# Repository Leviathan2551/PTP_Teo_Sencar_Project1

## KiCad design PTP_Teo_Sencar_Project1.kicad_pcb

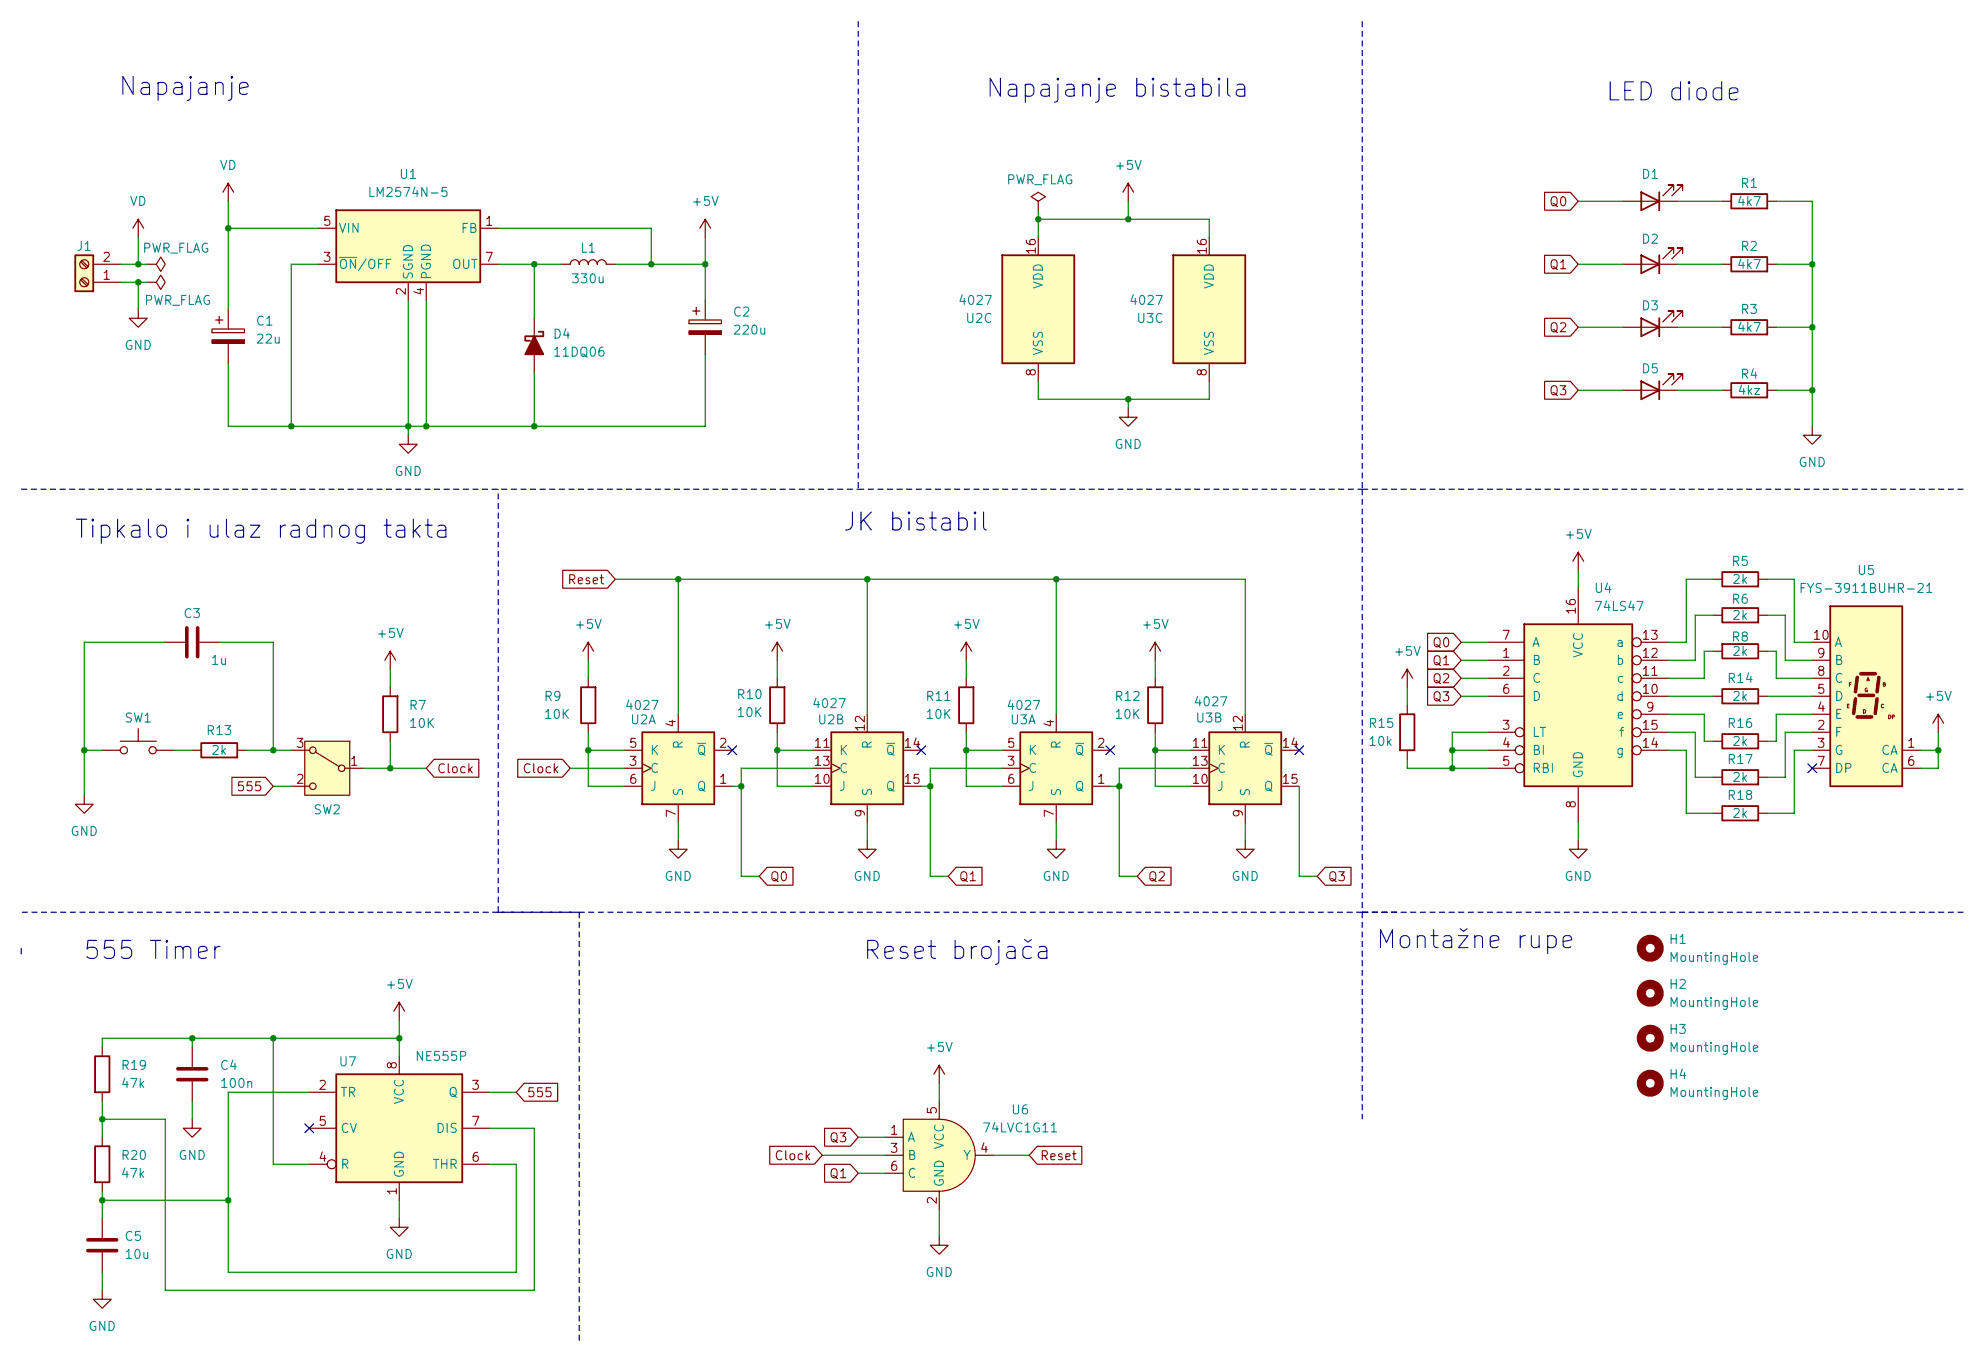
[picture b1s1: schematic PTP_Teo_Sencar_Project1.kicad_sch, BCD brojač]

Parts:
C1: 22u; CP_Radial_D5.0mm_P2.00mm; Manufacturer Part Number EWH1EM220D11OT
C2: 220u; CP_Radial_D5.0mm_P2.00mm; Manufacturer Part Number RD1A227M05011BB
C3: 1u; C_1206_3216Metric_Pad1.33x1.80mm_HandSolder; Manufacturer Part Number CL31B105KBHNNNE
C4: 100n; C_1206_3216Metric_Pad1.33x1.80mm_HandSolder; Manufacturer Part Number CL31B104KBCNNNC
C5: 10u; C_1206_3216Metric_Pad1.33x1.80mm_HandSolder; Manufacturer Part Number CL31A106KBHNNNE
D1, D2, D3, D5: LED; LED_D5.0mm
D4: 11DQ06; D_DO-41_SOD81_P12.70mm_Horizontal; Manufacturer Part Number 11DQ06TA
H1, H2, H3, H4: MountingHole; MountingHole_5.5mm
J1: Screw_Terminal_01x02; TerminalBlock_MetzConnect_Type011_RT05502HBLC_1x02_P5.00mm_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; Manufacturer Part Number DG301-5.0-02P-12-00A(H)
L1: 330u; L_Radial_D7.2mm_P3.00mm_Murata_1700; Manufacturer Part Number COIL0608-0.33
R1, R2, R3: 4k7; R_Axial_DIN0207_L6.3mm_D2.5mm_P10.16mm_Horizontal
R4: 4kz; R_Axial_DIN0207_L6.3mm_D2.5mm_P10.16mm_Horizontal
R5, R6, R8, R13, R14, R16, R17: 2k; R_1206_3216Metric_Pad1.30x1.75mm_HandSolder; Manufacturer Part Number 1206S4F2001T5E
R7, R9, R10, R11, R12: 10K; R_1206_3216Metric_Pad1.30x1.75mm_HandSolder
R15: 10k; R_1206_3216Metric_Pad1.30x1.75mm_HandSolder
R18: 2k; R_1206_3216Metric_Pad1.30x1.75mm_HandSolder; Manufacturer Part Number Resistor_SMD:R_1206_3216Metric_Pad1.30x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
R19, R20: 47k; R_1206_3216Metric_Pad1.30x1.75mm_HandSolder; Manufacturer Part Number 1206S4J0473T5E
SW1: SW_Push; SW_PUSH_6mm_H4.3mm; Manufacturer Part Number TACT-64N-F
SW2: SW_SPDT_312; SW_Slide_SPDT_Straight_CK_OS102011MS2Q; Manufacturer Part Number OS102011MS2QN1C
U1: LM2574N-5; DIP-8_W7.62mm_Socket_LongPads; Manufacturer Part Number LM2574N-5G
U2, U3: 4027; DIP-16_W7.62mm_Socket_LongPads; Manufacturer Part Number CD4027BMS
U4: 74LS47; DIP-16_W7.62mm_Socket_LongPads; Manufacturer Part Number SN74LS47N
U5: FYS-3911BUHR-21; HDSP-7401; Manufacturer Part Number FYS-3911BUHR-21
U6: 74LVC1G11; SOT-23-6; Manufacturer Part Number SN74LVC1G11DBVR
U7: NE555P; DIP-8_W7.62mm; Manufacturer Part Number NE555P

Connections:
555: SW2.2 (C), U7.3 (Q)
+5V: C2.1, C4.1, L1.2, R7.2, R9.2, R10.2, R11.2, R12.2, R15.1, R19.1, U1.1 (FB), U2.16 (VDD), U3.16 (VDD), U4.16 (VCC), U5.1 (CA), U5.6 (CA), U6.5 (VCC), U7.4 (R), U7.8 (VCC)
Clock: R7.1, SW2.1 (B), U2.3 (C), U6.3 (B)
GND: C1.2, C2.2, C3.1, C4.2, C5.2, D4.2 (A), J1.1, R1.2, R2.2, R3.2, R4.2, SW1.1, U1.2 (SGND), U1.3 (~ON/OFF), U1.4 (PGND), U2.7 (S), U2.8 (VSS), U2.9 (S), U3.7 (S), U3.8 (VSS), U3.9 (S), U4.8 (GND), U6.2 (GND), U7.1 (GND)
unnamed: D1.1 (K), R1.1
unnamed: D2.1 (K), R2.1
unnamed: D3.1 (K), R3.1
unnamed: D4.1 (K), L1.1, U1.7 (OUT)
unnamed: D5.1 (K), R4.1
unnamed: R13.1, SW1.2
unnamed: C3.2, R13.2, SW2.3 (A)
unnamed: R9.1, U2.5 (K), U2.6 (J)
unnamed: R10.1, U2.10 (J), U2.11 (K)
unnamed: R11.1, U3.5 (K), U3.6 (J)
unnamed: R12.1, U3.10 (J), U3.11 (K)
unnamed: R15.2, U4.3 (LT), U4.4 (BI), U4.5 (RBI)
unnamed: R5.1, U4.13 (a)
unnamed: R6.1, U4.12 (b)
unnamed: R8.2, U4.11 (c)
unnamed: R14.1, U4.10 (d)
unnamed: R16.1, U4.9 (e)
unnamed: R17.1, U4.15 (f)
unnamed: R18.1, U4.14 (g)
unnamed: R5.2, U5.10 (A)
unnamed: R6.2, U5.9 (B)
unnamed: R8.1, U5.8 (C)
unnamed: R14.2, U5.5 (D)
unnamed: R16.2, U5.4 (E)
unnamed: R17.2, U5.2 (F)
unnamed: R18.2, U5.3 (G)
unnamed: R19.2, R20.1, U7.7 (DIS)
unnamed: C5.1, R20.2, U7.2 (TR), U7.6 (THR)
Q0: D1.2 (A), U2.1 (Q), U2.13 (C), U4.7 (A)
Q1: D2.2 (A), U2.15 (Q), U3.3 (C), U4.1 (B), U6.6 (C)
Q2: D3.2 (A), U3.1 (Q), U3.13 (C), U4.2 (C)
Q3: D5.2 (A), U3.15 (Q), U4.6 (D), U6.1 (A)
Reset: U2.4 (R), U2.12 (R), U3.4 (R), U3.12 (R), U6.4 (Y)
VD: C1.1, J1.2, U1.5 (VIN)

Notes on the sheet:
555 Timer
Montažne rupe
Napajanje
LED diode
Tipkalo i ulaz radnog takta
Reset brojača
Napajanje bistabila
JK bistabil

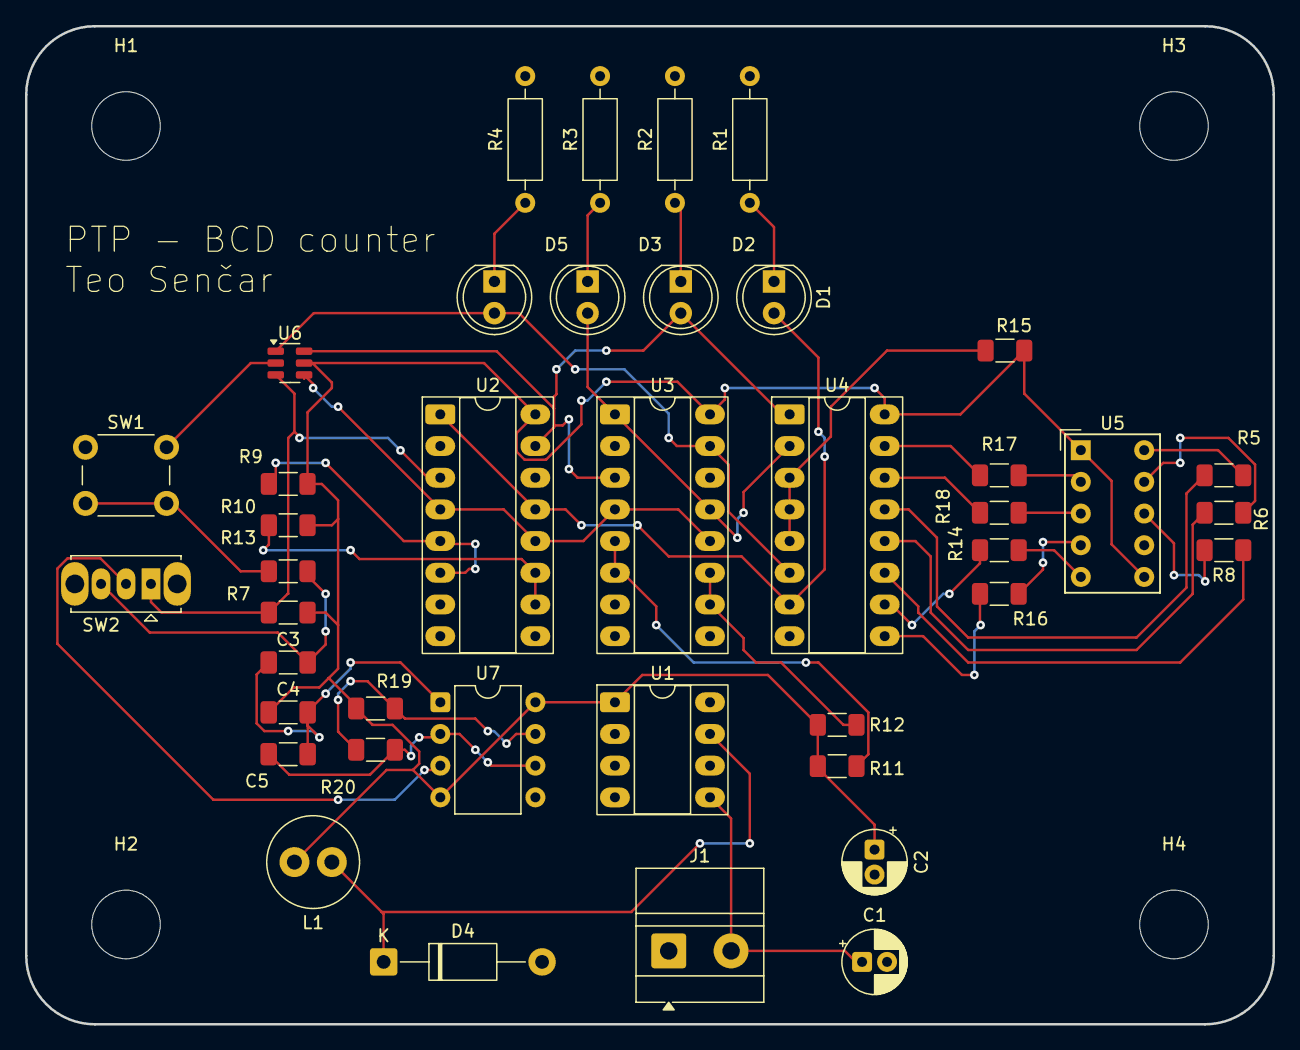
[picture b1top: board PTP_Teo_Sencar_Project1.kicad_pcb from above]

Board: 2 copper layers, 100.0 x 80.0 mm, 45 parts (0 on the bottom side), 38 nets.

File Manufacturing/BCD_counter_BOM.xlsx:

Reference | Qty | Value | Footprint | Manufacturer | Manufacturer Part Number
C1 | 1 | 22u | Capacitor_THT:CP_Radial_D5.0mm_P2.00mm | AISHI | EWH1EM220D11OT
C2 | 1 | 220u | Capacitor_THT:CP_Radial_D5.0mm_P2.00mm | SAMWHA | RD1A227M05011BB
C3 | 1 | 1u | Capacitor_SMD:C_1206_3216Metric_Pad1.33x1.80mm_HandSolder | SAMSUNG | CL31B105KBHNNNE
C4 | 1 | 100n | Capacitor_SMD:C_1206_3216Metric_Pad1.33x1.80mm_HandSolder | SAMSUNG | CL31B104KBCNNNC
C5 | 1 | 10u | Capacitor_SMD:C_1206_3216Metric_Pad1.33x1.80mm_HandSolder | SAMSUNG | CL31A106KBHNNNE
D1,D2,D3,D5 | 4 | LED | LED_THT:LED_D5.0mm
D4 | 1 | 11DQ06 | Diode_THT:D_DO-41_SOD81_P12.70mm_Horizontal | SMC DIODE SOLUTIONS | 11DQ06TA
H1,H2,H3,H4 | 4 | MountingHole | MountingHole:MountingHole_5.5mm
J1 | 1 | Screw_Terminal_01x02 | TerminalBlock_MetzConnect:TerminalBlock_MetzConnect_Type011_RT05502HBLC_1x02_P5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 | DEGSON ELECTRONICS | DG301-5.0-02P-12-00A(H)
L1 | 1 | 330u | Inductor_THT:L_Radial_D7.2mm_P3.00mm_Murata_1700 | FERROCORE | COIL0608-0.33
R1,R2,R3,R4 | 4 | 4k7 | Resistor_THT:R_Axial_DIN0207_L6.3mm_D2.5mm_P10.16mm_Horizontal
R5,R6,R8,R13,R14,R16,R17,R18 | 8 | 2k | Resistor_SMD:R_1206_3216Metric_Pad1.30x1.75mm_HandSolder | ROYALOHM | 1206S4F2001T5E
R7,R9,R10,R11,R12,R15 | 6 | 10k | Resistor_SMD:R_1206_3216Metric_Pad1.30x1.75mm_HandSolder
R19,R20 | 2 | 47k | Resistor_SMD:R_1206_3216Metric_Pad1.30x1.75mm_HandSolder | ROYALOHM | 1206S4J0473T5E
SW1 | 1 | SW_Push | Button_Switch_THT:SW_PUSH_6mm_H4.3mm | microswitch TACT | TACT-64N-F
SW2 | 1 | ~ | Button_Switch_THT:SW_Slide_SPDT_Straight_CK_OS102011MS2Q | C&K | OS102011MS2QN1C
U1 | 1 | LM2574N-5 | Package_DIP:DIP-8_W7.62mm_Socket_LongPads | ONSEMI | LM2574N-5G
U2,U3 | 2 | 4027 | Package_DIP:DIP-16_W7.62mm_Socket_LongPads | RENESAS | CD4027BMS
U4 | 1 | 74LS47 | Package_DIP:DIP-16_W7.62mm_Socket_LongPads | TEXAS INSTRUMENTS | SN74LS47N
U5 | 1 | FYS-3911BUHR-21 | Display_7Segment:HDSP-7401 | FORYARD | FYS-3911BUHR-21
U6 | 1 | 74LVC1G11 | Package_TO_SOT_SMD:SOT-23-6 | TEXAS INSTRUMENTS | SN74LVC1G11DBVR
U7 | 1 | NE555P | Package_DIP:DIP-8_W7.62mm | TEXAS INSTRUMENTS | NE555P

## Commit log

2025-10-21 Ispunjena sastavnica
2025-10-28 Dodan NE555
2025-11-04 Footprint i simbol
2025-11-11 Popunjeni parametri komponenata
2025-11-12 Dovršeni footprinti
2025-11-25 Postavljanje komponenata
2025-12-09 Spajanje vodova
2025-12-16 Gerber fileovi, BOM
2026-01-20 Initial Comit
